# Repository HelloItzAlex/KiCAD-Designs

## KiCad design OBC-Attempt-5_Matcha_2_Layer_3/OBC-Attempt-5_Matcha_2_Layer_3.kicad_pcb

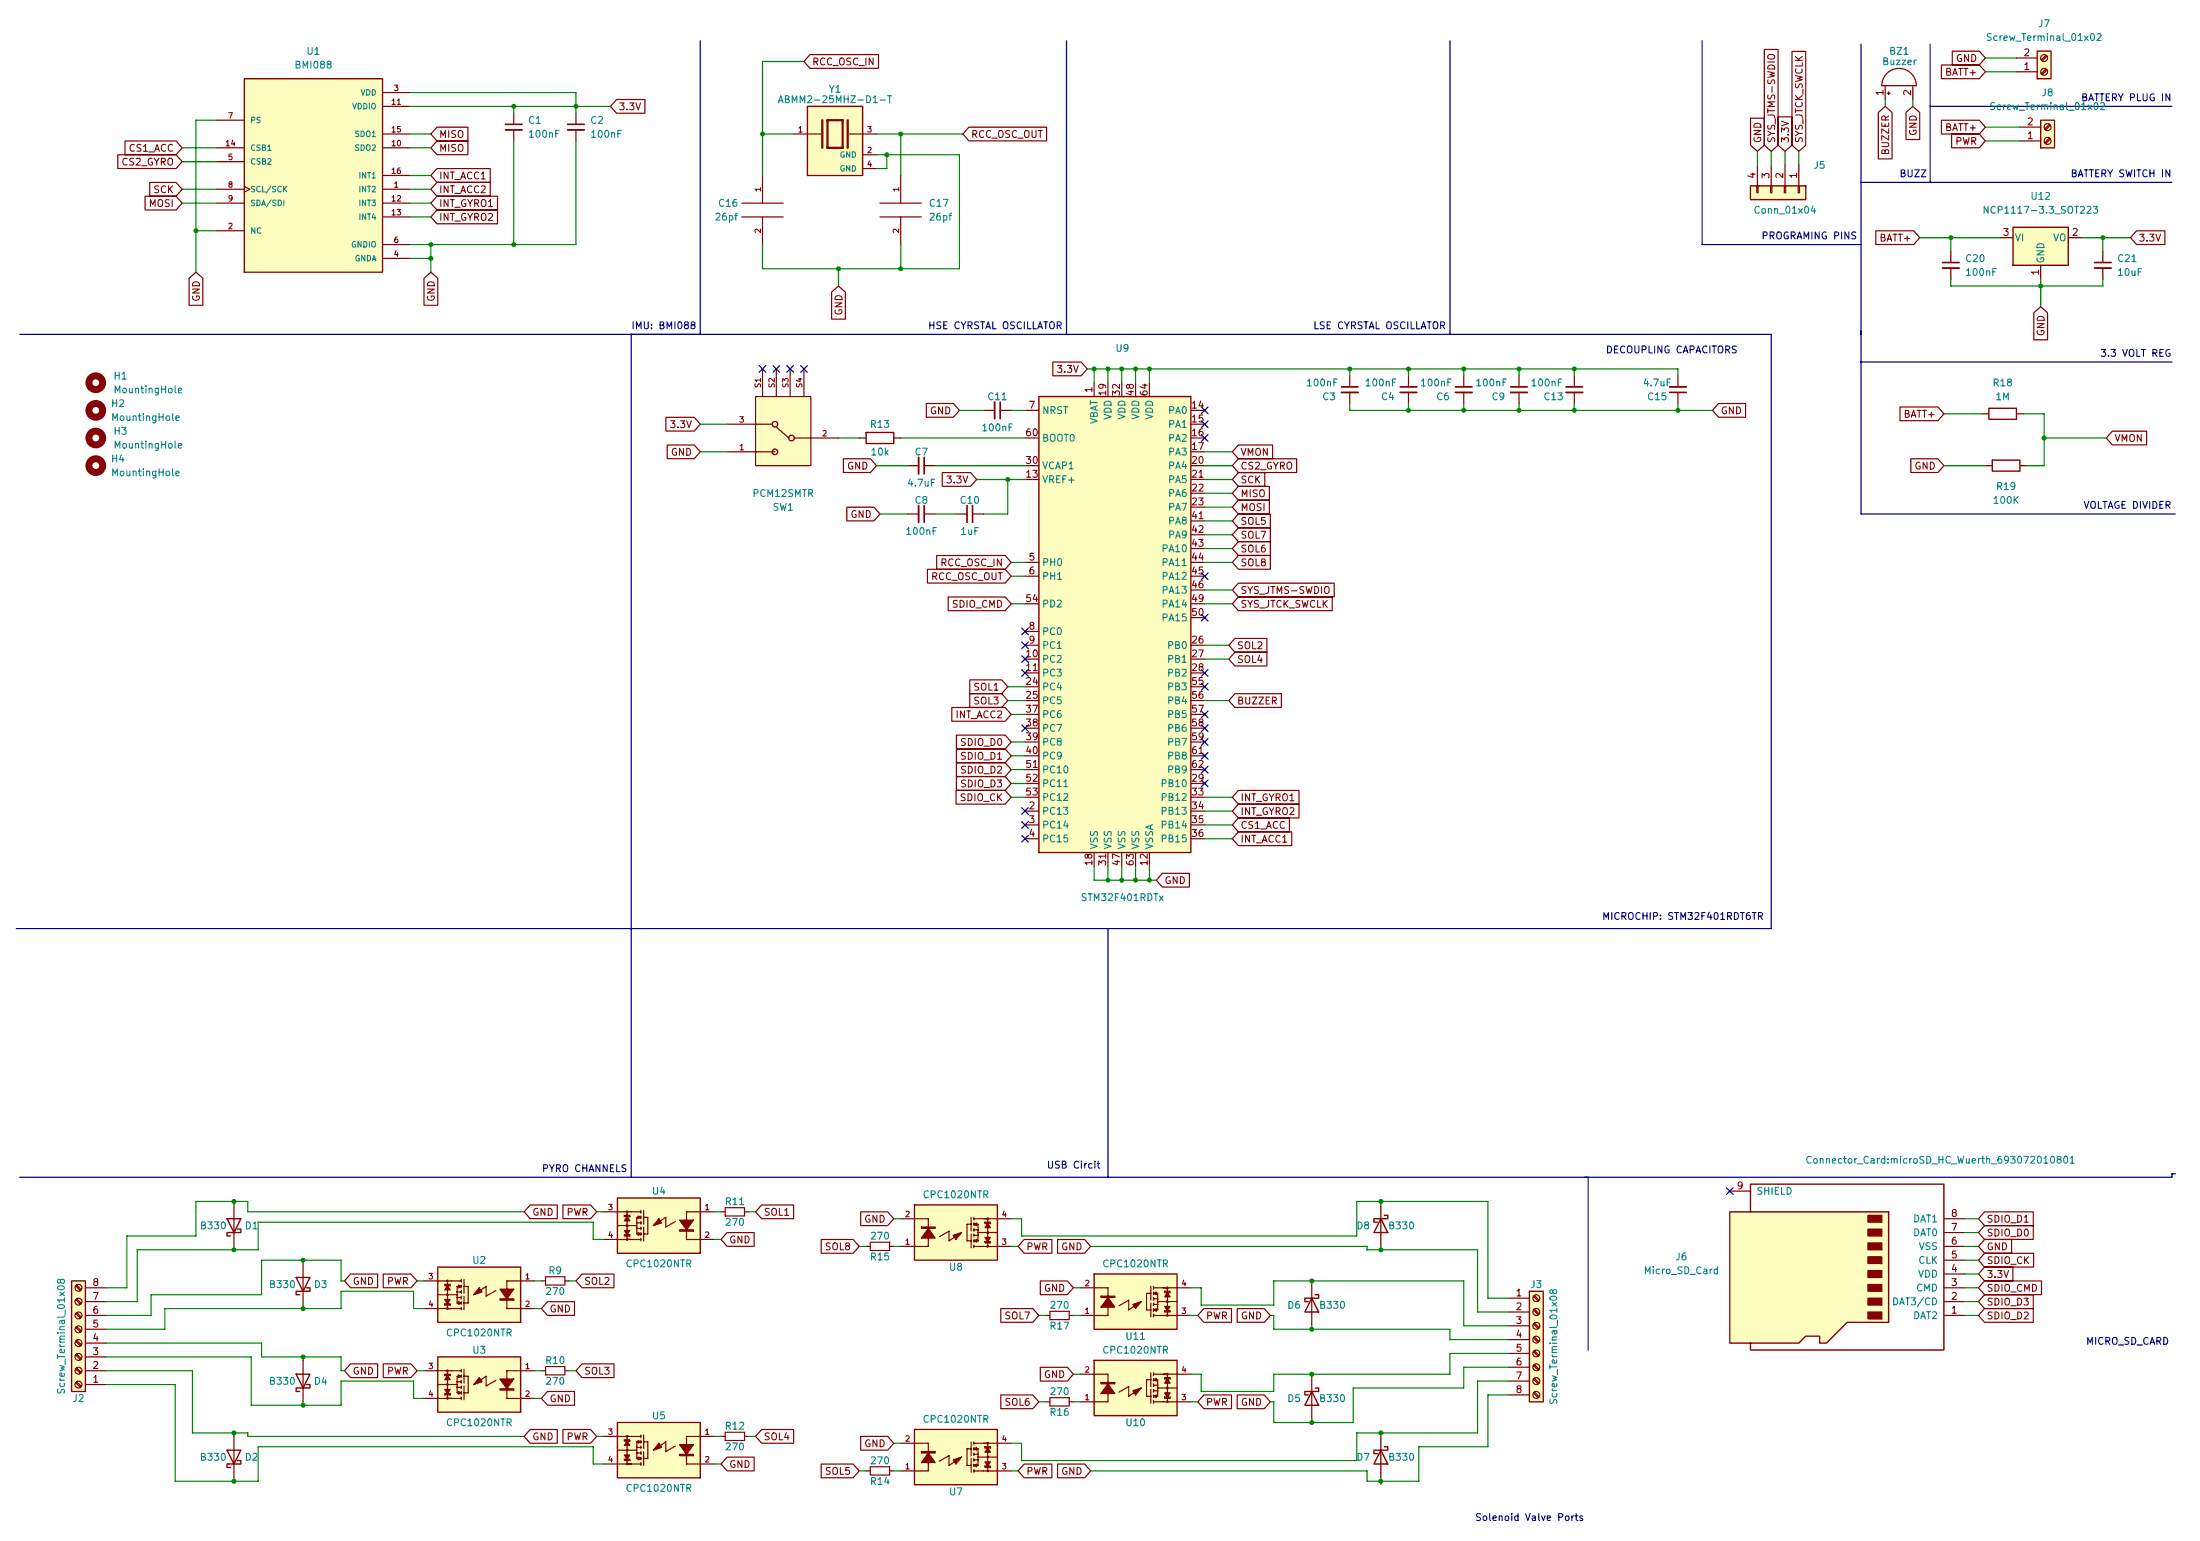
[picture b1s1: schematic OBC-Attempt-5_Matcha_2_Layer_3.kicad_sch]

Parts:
BZ1: Buzzer; Buzzer_TDK_PS1240P02BT_D12.2mm_H6.5mm
C1, C2, C3, C4, C6, C8, C9, C11, C13: 100nF; C_0402_1005Metric
C7: 4.7uF; C_0402_1005Metric
C10: 1uF; C_0603_1608Metric
C15: 4.7uF; C_0603_1608Metric
C16, C17: 26pf; C_0402_1005Metric
C20: 100nF; C_0603_1608Metric
C21: 10uF; C_0603_1608Metric
D1, D2, D3, D4, D5, D6, D7, D8: B330; D_SMA
H1, H2, H3, H4: MountingHole; MountingHole_3.2mm_M3
J2, J3: Screw_Terminal_01x08; TerminalBlock_Phoenix_MPT-0,5-8-2.54_1x08_P2.54mm_Horizontal
J5: Conn_01x04; PinHeader_1x04_P2.54mm_Vertical
J6: Micro_SD_Card; microSD_HC_Wuerth_693072010801
J7, J8: Screw_Terminal_01x02; TerminalBlock_Phoenix_MPT-0,5-2-2.54_1x02_P2.54mm_Horizontal
R9, R10, R11, R12, R14, R15, R16, R17: 270; R_0603_1608Metric
R13: 10k; R_0603_1608Metric
R18: 1M; R_0603_1608Metric
R19: 100K; R_0603_1608Metric
SW1: PCM12SMTR; SW_PCM12SMTR
U1: BMI088
U2, U3, U4, U5, U7, U8, U10, U11: CPC1020NTR; 4-SOP
U9: STM32F401RDTx; LQFP-64_10x10mm_P0.5mm
U12: NCP1117-3.3_SOT223; SOT-223-3_TabPin2
Y1: ABMM2-25MHZ-D1-T; XTAL_ABMM2-25.000MHZ-D1-T; PARTREV 01.18.13

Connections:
3.3V: C1.1, C2.1, C3.1, C4.1, C6.1, C9.1, C10.1, C13.1, C15.2, C21.1, J5.2, J6.4 (VDD), SW1.3, U1.3 (VDD), U1.11 (VDDIO), U9.1 (VBAT), U9.13 (VREF+), U9.19 (VDD), U9.32 (VDD), U9.48 (VDD), U9.64 (VDD), U12.2 (VO)
BATT+: C20.1, J7.1, J8.2, R18.1, U12.3 (VI)
BUZZER: BZ1.1 (-), U9.56 (PB4)
CS1_ACC: U1.14 (CSB1), U9.35 (PB14)
CS2_GYRO: U1.5 (CSB2), U9.20 (PA4)
GND: BZ1.2 (+), C1.2, C2.2, C3.2, C4.2, C6.2, C7.2, C8.2, C9.2, C11.2, C13.2, C15.1, C16.2, C17.2, C20.2, C21.2, D1.2 (A), D2.2 (A), D3.2 (A), D4.2 (A), D5.2 (A), D6.2 (A), D7.2 (A), D8.2 (A), J2.2, J2.4, J2.6, J2.8, J3.2, J3.4, J3.6, J3.8, J5.4, J6.6 (VSS), J7.2, R19.2, SW1.1, U1.2 (NC), U1.4 (GNDA), U1.6 (GNDIO), U1.7 (PS), U2.2, U3.2, U4.2, U5.2, U7.2, U8.2, U9.12 (VSSA), U9.18 (VSS), U9.31 (VSS), U9.47 (VSS), U9.63 (VSS), U10.2, U11.2, U12.1 (GND), Y1.2 (GND), Y1.4 (GND)
INT_ACC1: U1.16 (INT1), U9.36 (PB15)
INT_ACC2: U1.1 (INT2), U9.37 (PC6)
INT_GYRO1: U1.12 (INT3), U9.33 (PB12)
INT_GYRO2: U1.13 (INT4), U9.34 (PB13)
MISO: U1.10 (SDO2), U1.15 (SDO1), U9.22 (PA6)
MOSI: U1.9 (SDA/SDI), U9.23 (PA7)
unnamed: C7.1, U9.30 (VCAP1)
unnamed: C8.1, C10.2
unnamed: C11.1, U9.7 (NRST)
unnamed: D1.1 (K), J2.7, U4.4
unnamed: D2.1 (K), J2.1, U5.4
unnamed: D3.1 (K), J2.5, U2.4
unnamed: D4.1 (K), J2.3, U3.4
unnamed: D5.1 (K), J3.5, U10.4
unnamed: D6.1 (K), J3.3, U11.4
unnamed: D7.1 (K), J3.7, U7.4
unnamed: D8.1 (K), J3.1, U8.4
unnamed: R9.1, U2.1
unnamed: R10.1, U3.1
unnamed: R11.1, U4.1
unnamed: R12.1, U5.1
unnamed: R13.1, U9.60 (BOOT0)
unnamed: R13.2, SW1.2
unnamed: R14.1, U7.1
unnamed: R15.1, U8.1
unnamed: R16.1, U10.1
unnamed: R17.1, U11.1
PWR: J8.1, U2.3, U3.3, U4.3, U5.3, U7.3, U8.3, U10.3, U11.3
RCC_OSC_IN: C16.1, U9.5 (PH0), Y1.1
RCC_OSC_OUT: C17.1, U9.6 (PH1), Y1.3
SCK: U1.8 (SCL/SCK), U9.21 (PA5)
SDIO_CK: J6.5 (CLK), U9.53 (PC12)
SDIO_CMD: J6.3 (CMD), U9.54 (PD2)
SDIO_D0: J6.7 (DAT0), U9.39 (PC8)
SDIO_D1: J6.8 (DAT1), U9.40 (PC9)
SDIO_D2: J6.1 (DAT2), U9.51 (PC10)
SDIO_D3: J6.2 (DAT3/CD), U9.52 (PC11)
SOL1: R11.2, U9.24 (PC4)
SOL2: R9.2, U9.26 (PB0)
SOL3: R10.2, U9.25 (PC5)
SOL4: R12.2, U9.27 (PB1)
SOL5: R14.2, U9.41 (PA8)
SOL6: R16.2, U9.43 (PA10)
SOL7: R17.2, U9.42 (PA9)
SOL8: R15.2, U9.44 (PA11)
SYS_JTCK_SWCLK: J5.1, U9.49 (PA14)
SYS_JTMS-SWDIO: J5.3, U9.46 (PA13)
VMON: R18.2, R19.1, U9.17 (PA3)

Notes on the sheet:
DECOUPLING CAPACITORS
IMU: BMI088
3.3 VOLT REG
HSE CYRSTAL OSCILLATOR
PROGRAMING PINS
LSE CYRSTAL OSCILLATOR
MICRO_SD_CARD
MICROCHIP: STM32F401RDT6TR
VOLTAGE DIVIDER
BATTERY PLUG IN
BUZZ
Solenoid Valve Ports
USB Circit
PYRO CHANNELS
BATTERY SWITCH IN

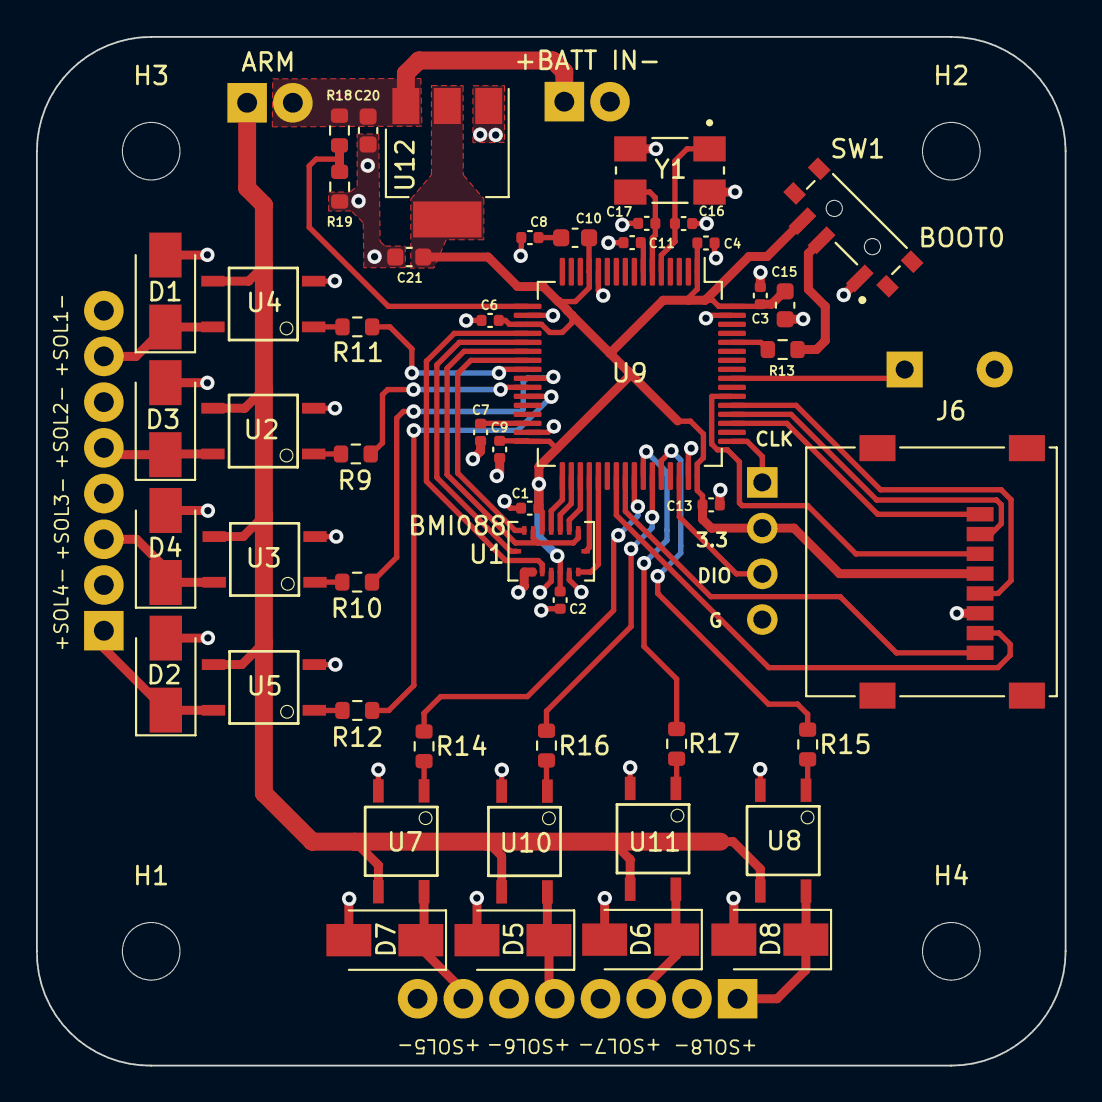
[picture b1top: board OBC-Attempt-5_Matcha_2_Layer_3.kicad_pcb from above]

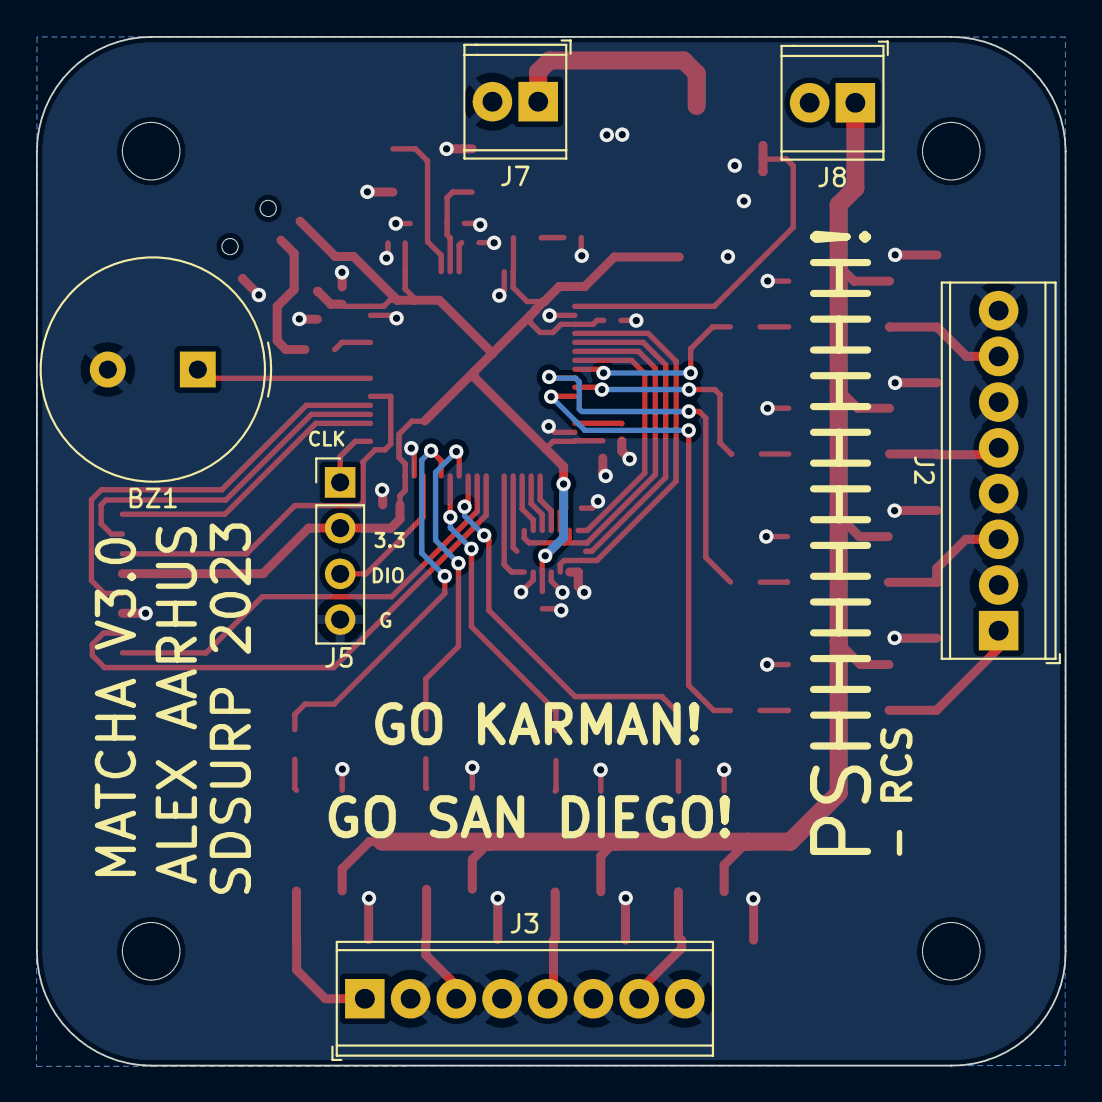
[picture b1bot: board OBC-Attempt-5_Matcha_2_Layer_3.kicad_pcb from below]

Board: 2 copper layers, 57.1 x 57.1 mm, 59 parts (6 on the bottom side), 54 nets.

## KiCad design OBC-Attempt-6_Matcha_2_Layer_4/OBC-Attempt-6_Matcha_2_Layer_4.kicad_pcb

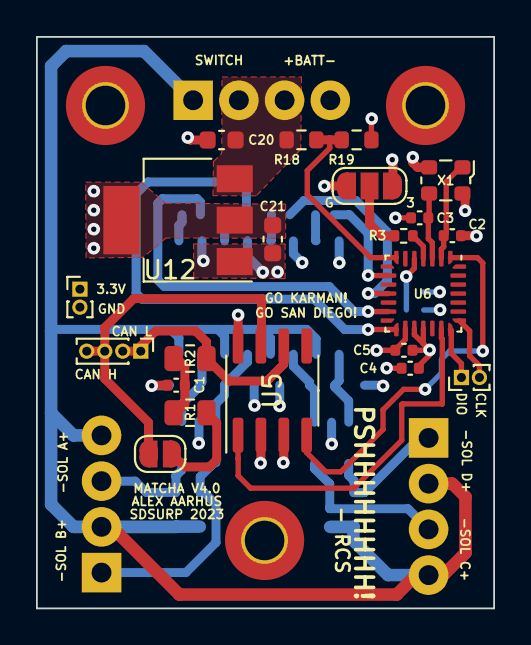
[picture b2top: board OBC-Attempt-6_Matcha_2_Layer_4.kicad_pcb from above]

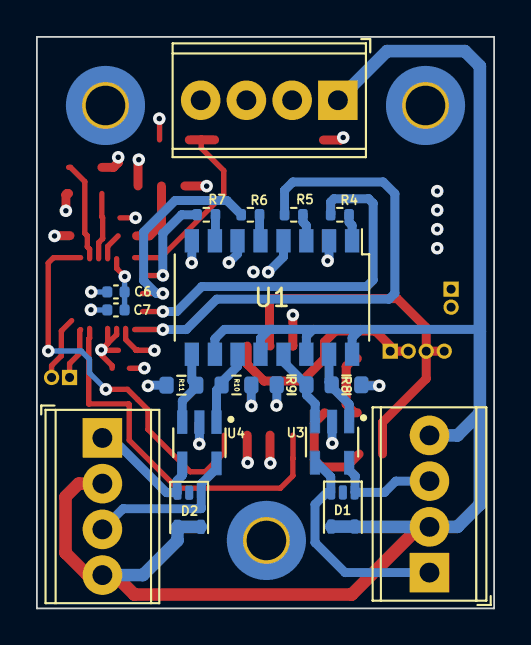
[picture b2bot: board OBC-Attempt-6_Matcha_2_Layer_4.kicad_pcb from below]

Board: 4 copper layers, 25.4 x 31.8 mm, 42 parts (18 on the bottom side), 33 nets.

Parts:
C1: 4.7nF; C_0402_1005Metric
C2, C3: 20pF; C_0402_1005Metric
C4: 4u7; C_0402_1005Metric
C5: 1uF; C_0402_1005Metric
C6: .1uF; C_0402_1005Metric
C7: 10nF; C_0402_1005Metric
C20: 100nF; C_0603_1608Metric
C21: 10uF; C_0603_1608Metric
D1, D2: CVJ10F30
H1, H2, H3: MountingHole_Pad; MountingHole_2.2mm_M2_Pad_TopBottom
J1: CAN Header; PinHeader_1x04_P1.00mm_Vertical
J2: SOL A; TerminalBlock_Phoenix_MPT-0,5-4-2.54_1x04_P2.54mm_Horizontal
J3: SOL B; TerminalBlock_Phoenix_MPT-0,5-4-2.54_1x04_P2.54mm_Horizontal
J4: Screw_Terminal_01x04; TerminalBlock_Phoenix_MPT-0,5-4-2.54_1x04_P2.54mm_Horizontal
J5, J6: Conn_01x02_Male; PinHeader_1x02_P1.00mm_Vertical
R1, R2: 60 ohm; R_0805_2012Metric
R3: 10k; R_0402_1005Metric
R4, R5, R6, R7: R; R_0402_1005Metric
R8, R9, R10, R11: R; R_0603_1608Metric
R18: 1M; R_0603_1608Metric
R19: 100K; R_0603_1608Metric
SW1: SW_SPST; SolderJumper-2_P1.3mm_Open_RoundedPad1.0x1.5mm
SW2: SW_SPDT; SolderJumper-3_P1.3mm_Open_RoundedPad1.0x1.5mm_NumberLabels
U1: LTV-247; SOP-16_4.4x10.4mm_P1.27mm
U3, U4: QS5K2TR; SOT95P280X100-5N
U5: SN65HVD230; SOIC-8_3.9x4.9mm_P1.27mm
U6: STM32F042G4Ux; QFN-28_4x4mm_P0.5mm
U12: NCP1117-3.3_SOT223; SOT-223-3_TabPin2
X1: ECS-2520MV-xxx-xx; Oscillator_SMD_ECS_2520MV-xxx-xx-4Pin_2.5x2.0mm

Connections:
3.3V: C4.1, C5.1, C6.1, C7.1, C21.1, J6.1, SW2.3 (C), U5.3 (VCC), U6.5 (VDDA), U6.17 (VDD), U6.18 (VDDIO2), U12.2 (VO)
BATT+: C20.1, J4.2, J4.3, R18.1, U12.3 (VI)
BOOT0: R3.1, U6.4 (NRST)
CAN_H: J1.3, J1.4, SW1.2 (B), U5.7 (CANH)
CAN_L: J1.1, J1.2, R2.2, U5.6 (CANL)
CAN_RX: U5.4 (R), U6.1 (PB8)
CAN_TX: U5.1 (D), U6.20 (PA10/PA12)
GND: C1.2, C2.2, C3.2, C4.2, C5.2, C6.2, C7.2, C20.2, C21.2, H1.1, H2.1, H3.1, J4.4, J6.2, R8.1, R9.1, R10.1, R11.1, R19.2, SW2.1 (A), U1.2, U1.4, U1.6, U1.8, U3.2, U4.2, U5.2 (GND), U5.8 (Rs), U6.16 (VSSA), U12.1 (GND), X1.2 (GND), X1.4 (VDD)
unnamed: C1.1, R1.2, R2.1
unnamed: R1.1, SW1.1 (A)
unnamed: R3.2, SW2.2 (B)
unnamed: R4.1, U1.1
unnamed: R5.1, U1.3
unnamed: R6.1, U1.5
unnamed: R7.1, U1.7
unnamed: R8.2, U1.15, U3.1
unnamed: R9.2, U1.13, U3.3
unnamed: R10.2, U1.11, U4.1
unnamed: R11.2, U1.9, U4.3
PWR: D1.4 (D2OUT), D1.5 (D1OUT), D2.4 (D2OUT), D2.5 (D1OUT), J2.2, J2.4, J3.2, J3.4, J4.1, U1.10, U1.12, U1.14, U1.16
RCC_OSC_IN: C2.1, U6.2 (PF0), X1.1 (Tri-State)
RCC_OSC_OUT: C3.1, U6.3 (PF1), X1.3 (OUT)
SOL1: R4.2, U6.13 (PA7)
SOL2: R5.2, U6.15 (PB1)
SOL3: R6.2, U6.11 (PA5)
SOL4: R7.2, U6.9 (PA3)
SOLA: D1.1 (D1IN), J2.3, U3.5
SOLB: D1.3 (D2IN), J2.1, U3.4
SOLC: D2.1 (D1IN), J3.3, U4.5
SOLD: D2.3 (D2IN), J3.1, U4.4
SYS_JTCK_SWCLK: J5.2, U6.22 (PA14)
SYS_JTMS-SWDIO: J5.1, U6.21 (PA13)
VMON: R18.2, R19.1, U6.7 (PA1)

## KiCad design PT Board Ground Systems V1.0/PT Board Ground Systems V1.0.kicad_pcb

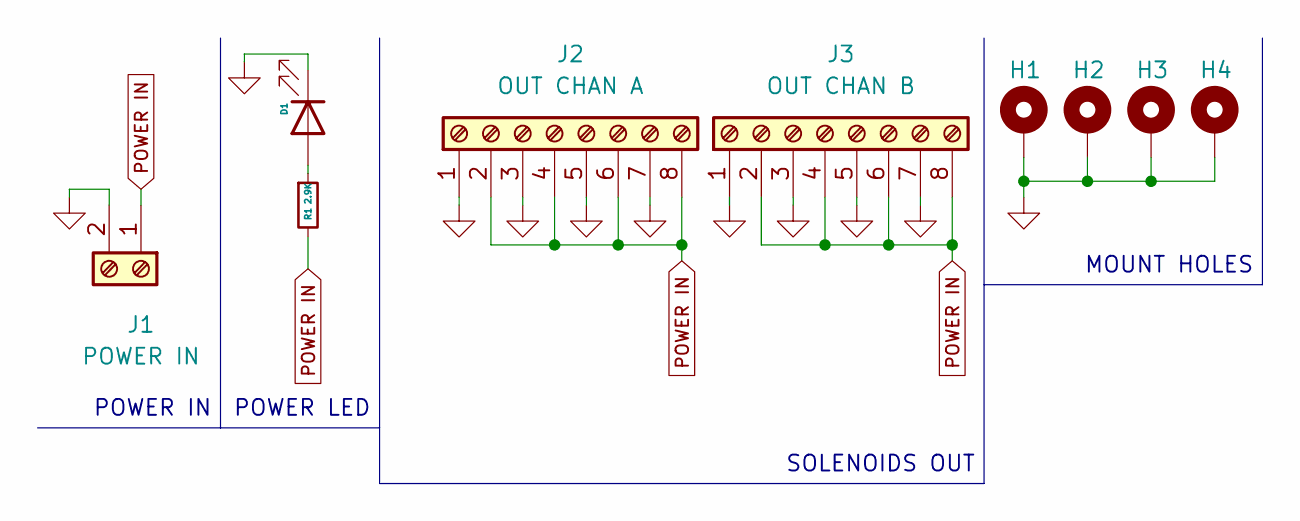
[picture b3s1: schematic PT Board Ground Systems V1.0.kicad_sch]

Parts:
D1: LED; LED_0805_2012Metric
H1, H2, H3, H4: MountingHole_Pad; MountingHole_3.2mm_M3_DIN965_Pad_TopBottom
J1: POWER IN; TerminalBlock_Phoenix_MPT-0,5-2-2.54_1x02_P2.54mm_Horizontal
J2: OUT CHAN A; TerminalBlock_Phoenix_MPT-0,5-8-2.54_1x08_P2.54mm_Horizontal
J3: OUT CHAN B; TerminalBlock_Phoenix_MPT-0,5-8-2.54_1x08_P2.54mm_Horizontal
R1: 2.9K; R_0603_1608Metric

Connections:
GND: D1.1 (K), H1.1, H2.1, H3.1, H4.1, J1.2, J2.1, J2.3, J2.5, J2.7, J3.1, J3.3, J3.5, J3.7
unnamed: D1.2 (A), R1.1
POWER IN: J1.1, J2.2, J2.4, J2.6, J2.8, J3.2, J3.4, J3.6, J3.8, R1.2

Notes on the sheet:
MOUNT HOLES
POWER IN
POWER LED
SOLENOIDS OUT

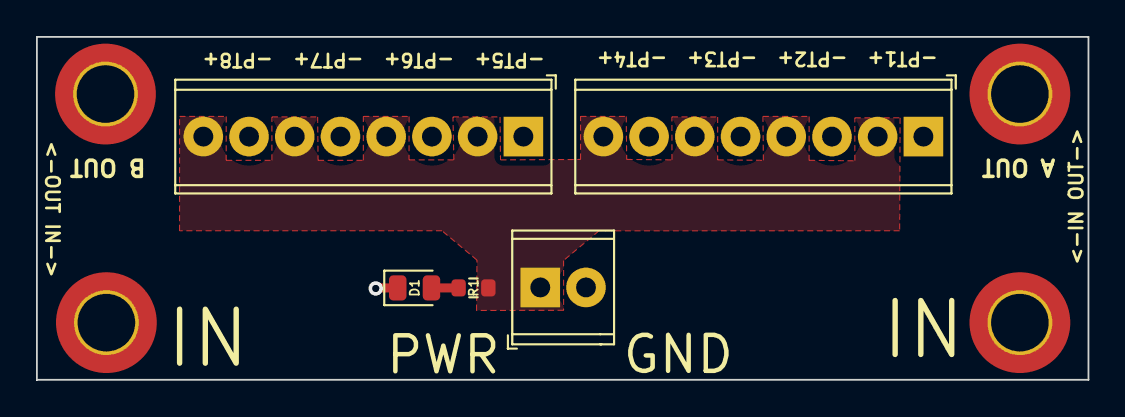
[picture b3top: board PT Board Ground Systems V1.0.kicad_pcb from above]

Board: 2 copper layers, 58.4 x 19.1 mm, 9 parts (0 on the bottom side), 3 nets.

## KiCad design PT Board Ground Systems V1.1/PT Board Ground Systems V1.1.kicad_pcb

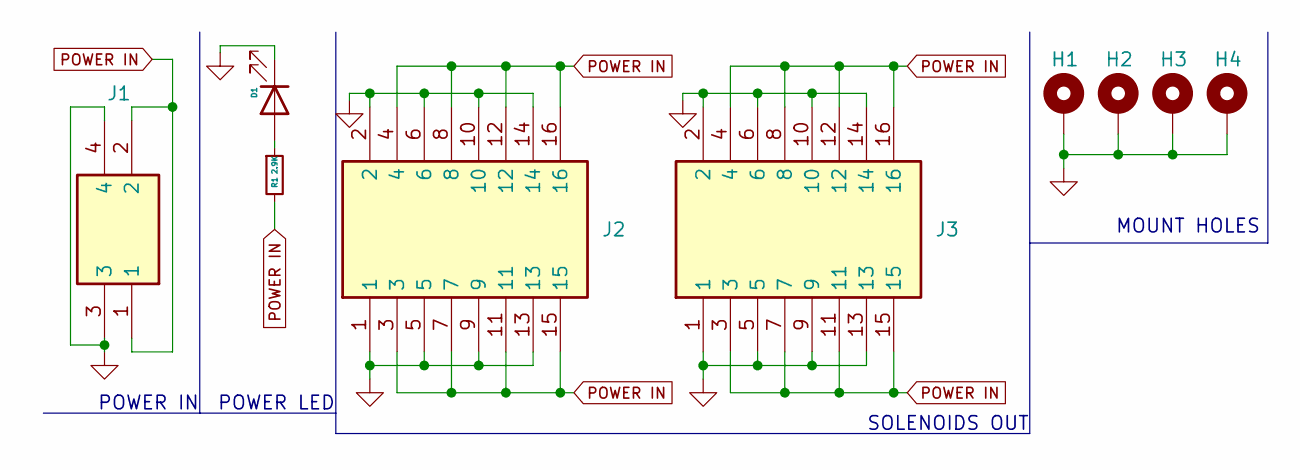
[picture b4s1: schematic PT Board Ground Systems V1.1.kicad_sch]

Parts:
D1: LED; LED_0805_2012Metric
H1, H2, H3, H4: MountingHole_Pad; MountingHole_3.2mm_M3_DIN965_Pad_TopBottom
J1: TBLH10V-350-02BK; RHDR4W80P550X350_2X2_770X850X1420P; Mouser Part Number 490-TBLH10V-350-02BK
J2, J3: TBLH10V-350-08BK; RHDR16W80P550X350_2X8_2870X850X1420P; Mouser Part Number 490-TBLH10V-350-08BK
R1: 2.9K; R_0603_1608Metric

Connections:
GND: D1.1 (K), H1.1, H2.1, H3.1, H4.1, J1.3, J1.4, J2.1, J2.2, J2.5, J2.6, J2.9, J2.10, J2.13, J2.14, J3.1, J3.2, J3.5, J3.6, J3.9, J3.10, J3.13, J3.14
unnamed: D1.2 (A), R1.1
POWER IN: J1.1, J1.2, J2.3, J2.4, J2.7, J2.8, J2.11, J2.12, J2.15, J2.16, J3.3, J3.4, J3.7, J3.8, J3.11, J3.12, J3.15, J3.16, R1.2

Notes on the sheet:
MOUNT HOLES
POWER IN
POWER LED
SOLENOIDS OUT

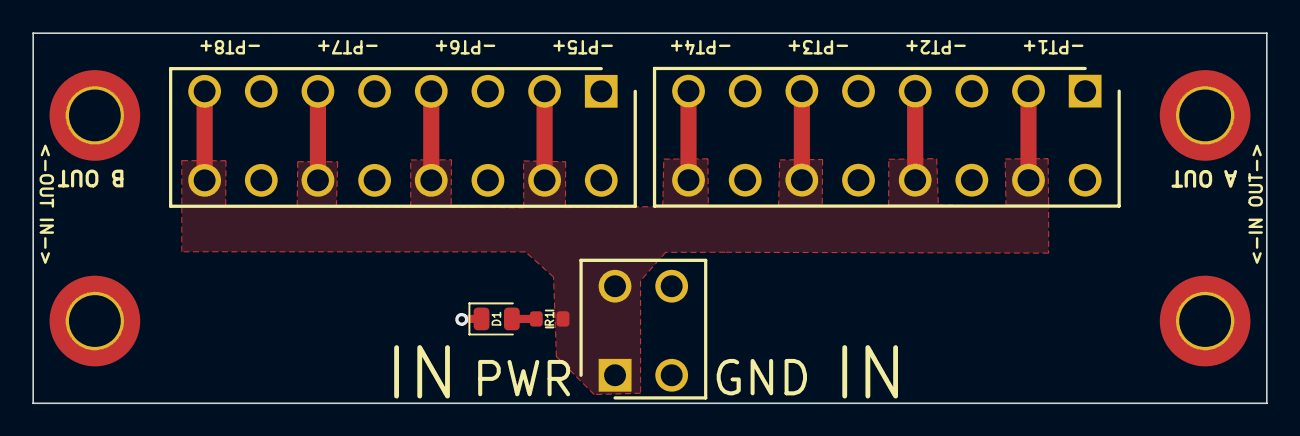
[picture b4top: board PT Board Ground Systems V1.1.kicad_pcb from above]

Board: 2 copper layers, 76.2 x 22.9 mm, 9 parts (0 on the bottom side), 3 nets.

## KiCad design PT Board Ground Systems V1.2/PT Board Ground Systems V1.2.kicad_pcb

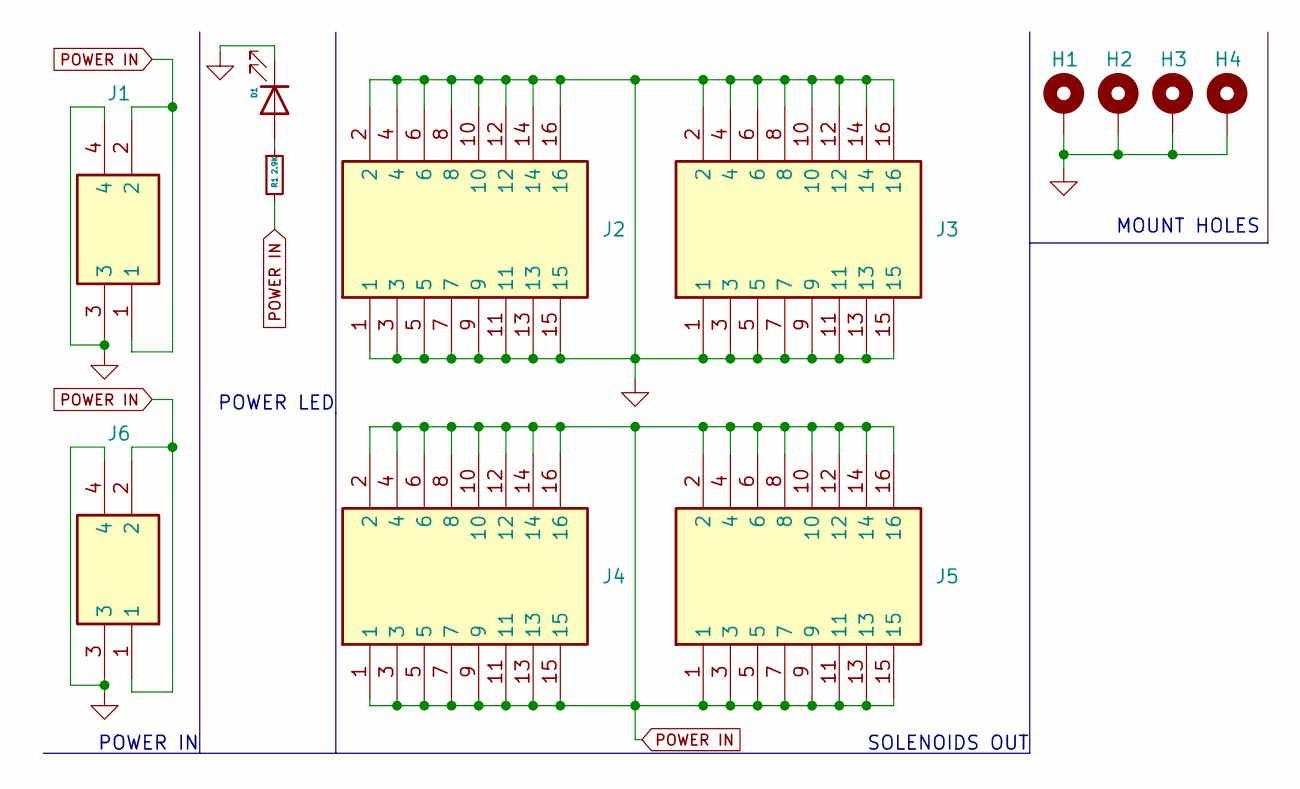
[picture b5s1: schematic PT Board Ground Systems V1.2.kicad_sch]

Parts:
D1: LED; LED_D3.0mm
H1, H2, H3, H4: MountingHole_Pad; MountingHole_3.2mm_M3_DIN965_Pad_TopBottom
J1, J6: TBLH10V-350-02BK; RHDR4W80P550X350_2X2_770X850X1420P; Mouser Part Number 490-TBLH10V-350-02BK
J2, J3, J4, J5: TBLH10V-350-08BK; RHDR16W80P550X350_2X8_2870X850X1420P; Mouser Part Number 490-TBLH10V-350-08BK
R1: 2.9K; R_Axial_DIN0204_L3.6mm_D1.6mm_P5.08mm_Horizontal

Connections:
GND: D1.1 (K), H1.1, H2.1, H3.1, H4.1, J1.3, J1.4, J2.1, J2.2, J2.3, J2.4, J2.5, J2.6, J2.7, J2.8, J2.9, J2.10, J2.11, J2.12, J2.13, J2.14, J2.15, J2.16, J3.1, J3.2, J3.3, J3.4, J3.5, J3.6, J3.7, J3.8, J3.9, J3.10, J3.11, J3.12, J3.13, J3.14, J3.15, J3.16, J6.3, J6.4
unnamed: D1.2 (A), R1.1
POWER IN: J1.1, J1.2, J4.1, J4.2, J4.3, J4.4, J4.5, J4.6, J4.7, J4.8, J4.9, J4.10, J4.11, J4.12, J4.13, J4.14, J4.15, J4.16, J5.1, J5.2, J5.3, J5.4, J5.5, J5.6, J5.7, J5.8, J5.9, J5.10, J5.11, J5.12, J5.13, J5.14, J5.15, J5.16, J6.1, J6.2, R1.2

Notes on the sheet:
MOUNT HOLES
POWER IN
POWER LED
SOLENOIDS OUT

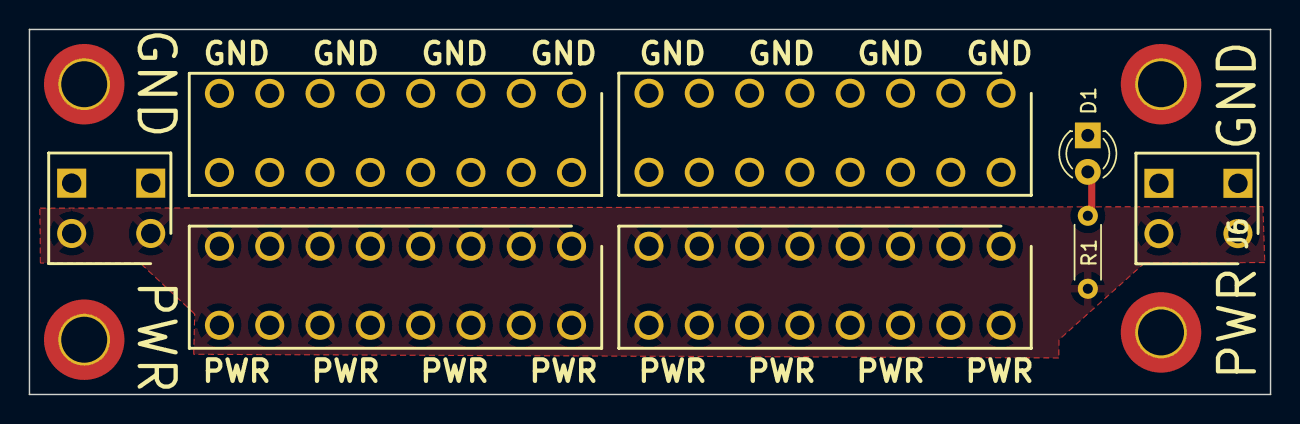
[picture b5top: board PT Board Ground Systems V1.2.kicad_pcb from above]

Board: 2 copper layers, 86.4 x 25.4 mm, 12 parts (0 on the bottom side), 3 nets.

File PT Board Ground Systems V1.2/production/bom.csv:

Designator,Footprint,Quantity,Value,LCSC Part #
D1,LED_D3.0mm,1,LED,
"H1, H2, H3, H4",MountingHole_3.2mm_M3_DIN965_Pad_TopBottom,4,MountingHole_Pad,
"J1, J6",RHDR4W80P550X350_2X2_770X850X1420P,2,TBLH10V-350-02BK,
"J2, J3, J4, J5",RHDR16W80P550X350_2X8_2870X850X1420P,4,TBLH10V-350-08BK,
R1,R_Axial_DIN0204_L3.6mm_D1.6mm_P5.08mm_Horizontal,1,2.9K,
